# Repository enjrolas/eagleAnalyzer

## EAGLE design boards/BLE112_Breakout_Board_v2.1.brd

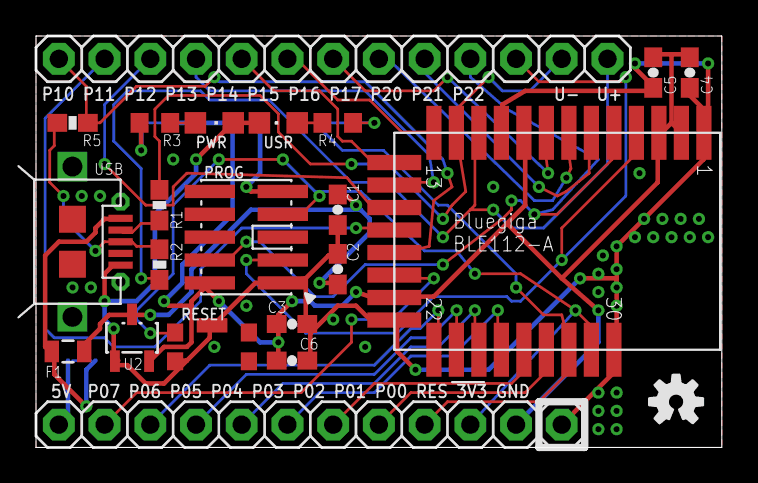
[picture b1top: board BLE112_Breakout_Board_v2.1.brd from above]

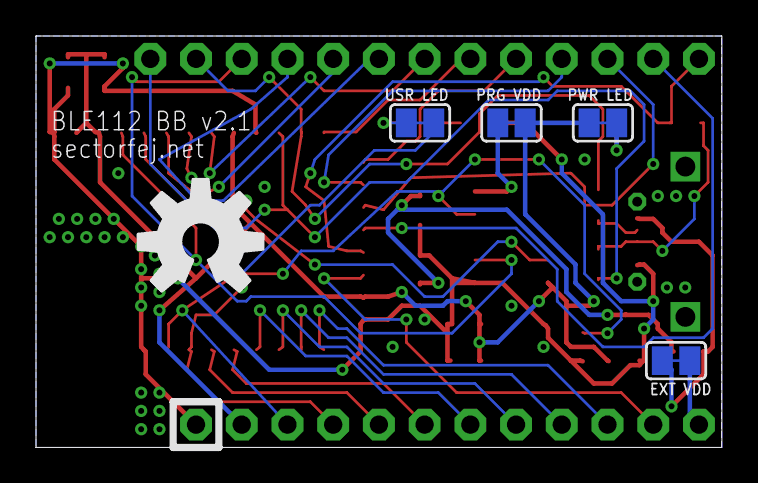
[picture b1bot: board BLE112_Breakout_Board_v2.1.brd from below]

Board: 2 copper layers, 38.1 x 22.9 mm, 27 parts (5 on the bottom side), 34 nets.

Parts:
C1: 0.47uF; 0603-CAP
C2, C3: 2.2uF; 0603-CAP
C4, C5, C6: 1uF; 0603-CAP
F1: 1K; 0805
JP1: BRK1; 1X12
JP2: BRK1; 1X13
OSHW1: OSHW-LOGOL; OSHW-LOGO-L
OSHW2: OSHW-LOGOS; OSHW-LOGO-S
PROG: CONN_5-2-FTSH-V; FTSH-105-DV
PWR: GREEN; CHIPLED_0805
R1, R2: 33; 0603-RES
R3, R4: 470; R0603
R5: 1.5K; 0603-RES
S1: RESET; 101-IG
SJ1: PRG VDD; SJ
SJ2: PWR LED; SJ
SJ3: USR LED; SJ
SJ4: EXT VDD; SJ
U1: BLE112-A
U2: MCP1700; SOT23-3
USB: MICROUSB-47589-0001
USR: BLUE; CHIPLED_0805

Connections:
3.3V: C3.1, C4.1, C5.1, C6.2, JP1.2, PROG.2, SJ1.2, SJ2.1, U1.AVDD1, U1.AVDD2, U1.DVDD, U1.VDD_USB, U2.2
5V: C1.1, C2.1, F1.1, U2.3
EXT5V: JP1.12, SJ4.2
GND: C1.2, C2.2, C3.2, C4.2, C5.2, C6.1, JP1.1, PROG.1, PWR.C, S1.2, S1.GND, U1.GND1, U1.GND2, U1.GND3, U1.GND4, U2.1, USB.GND, USR.C
unnamed: PWR.A, R3.2
unnamed: R3.1, SJ2.2
unnamed: R4.2, USR.A
unnamed: R4.1, SJ3.2
P0_0: JP1.4, SJ3.1, U1.P0_0
P0_1: JP1.5, U1.P0_1
P0_2: JP1.6, U1.P0_2
P0_3: JP1.7, U1.P0_3
P0_4: JP1.8, U1.P0_4
P0_5: JP1.9, U1.P0_5
P0_6: JP1.10, U1.P0_6
P0_7: JP1.11, U1.P0_7
P1_0: JP2.13, R5.2, U1.P1_0
P1_1: JP2.12, U1.P1_1
P1_2: JP2.11, U1.P1_2
P1_3: JP2.10, U1.P1_3
P1_4: JP2.9, U1.P1_4
P1_5: JP2.8, U1.P1_5
P1_6: JP2.7, U1.P1_6
P1_7: JP2.6, U1.P1_7
P2_0: JP2.5, U1.P2_0
P2_1: JP2.4, PROG.4, U1.P2_1
P2_2: JP2.3, PROG.3, U1.P2_2
PRG_VDD: PROG.9, SJ1.1
P_U+: R2.2, R5.1, USB.D+
P_U-: R1.2, USB.D-
RESET: JP1.3, PROG.7, S1.1, U1.RESET
USB+: JP2.1, R2.1, U1.USB+
USB-: JP2.2, R1.1, U1.USB-
VBUS: F1.2, SJ4.1, USB.VBUS

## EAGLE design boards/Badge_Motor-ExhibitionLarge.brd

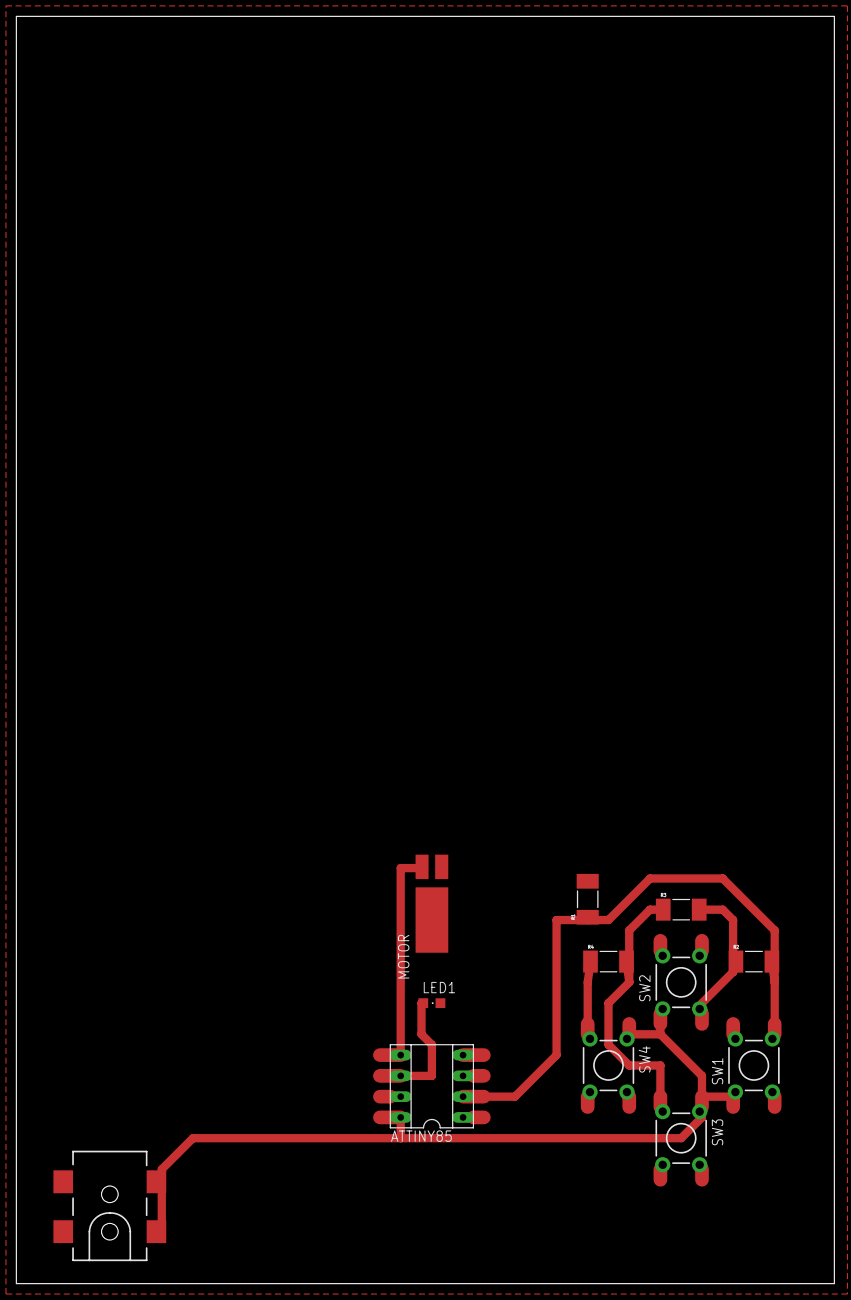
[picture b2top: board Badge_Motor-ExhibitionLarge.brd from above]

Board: 2 copper layers, 100.0 x 154.9 mm, 12 parts (0 on the bottom side), 8 nets.

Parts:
ATTINY85: SOCKET-08
LED1: CHIPLED_0805
MOTOR: VIB-MOTOR
POWER: 3-5VDC; POWER_JACK_SMD
R1, R2, R3, R4: R2010
SW1, SW2, SW3, SW4: TACTILE-PTH

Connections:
+3V: ATTINY85.8, POWER.GND, POWER.P$4, SW1.1, SW2.1, SW3.1, SW4.1
GND: ATTINY85.4, LED1.C, MOTOR.1, POWER.VIN0, R1.2
unnamed: ATTINY85.5, MOTOR.2
unnamed: ATTINY85.2, R1.1, R2.2, SW1.4
unnamed: ATTINY85.6, LED1.A
unnamed: R4.1, SW4.3
unnamed: R3.1, R4.2, SW3.3
unnamed: R2.1, R3.2, SW2.3

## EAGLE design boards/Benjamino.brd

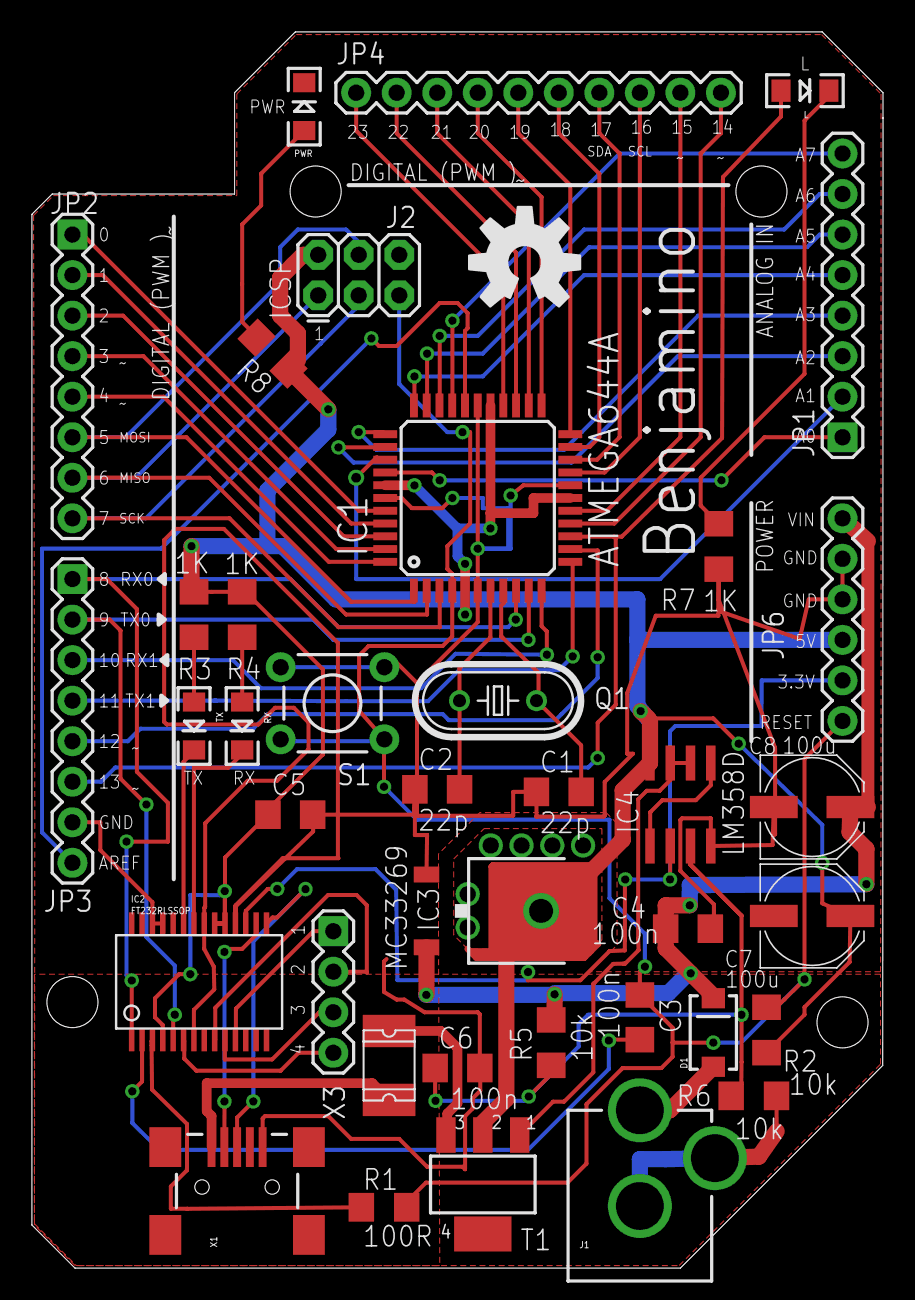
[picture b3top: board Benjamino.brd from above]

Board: 2 copper layers, 53.3 x 77.5 mm, 40 parts (1 on the bottom side), 60 nets.

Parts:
C1, C2: 22p; C1206
C3, C4, C5, C6: 100n; C1206
C7, C8: 100u; PANASONIC_D
D1: SMA-DIODE
F1: 0.5A; 1812L
IC1: ATMEGA644A; TQFP44
IC2: FT232RLSSOP; SSOP28DB
IC3: MC33269; DPACK
IC4: LM358D; SO08
J1: POWER_JACKPTH; POWER_JACK_PTH
J2: ICSP; 2X3
JP1, JP2, JP3: 1X08
JP4: 1X10
JP6: 1X06
L: LED-1206
PWR: LED-1206
Q1: HC49U-V
R1: 100R; R1206
R2, R5, R6: 10k; R1206
R3, R4, R7, R8: 1K; R1206
RX: LED-1206
S1: TACTILE-PTH
T1: SOT223
TX: LED-1206
U$1, U$2: OSHW-LOGO-L
X1: USBSMD; USB-MINIB
X3: 1X04

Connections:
3V3: IC2.17, IC4.2, JP6.2
AREF: IC1.29, JP3.8
GND: C1.1, C2.1, C4.2, C5.2, C6.2, C7.-, C8.-, IC1.6, IC1.18, IC1.28, IC1.39, IC2.7, IC2.18, IC2.21, IC2.25, IC2.26, IC3.1, IC4.4, J1.GND, J1.GNDBREAK, J2.6, JP3.7, JP6.4, JP6.5, PWR.C, R6.1, R7.1, S1.3, S1.4, X1.GND
MISO: IC1.2, J2.1, JP2.7
MOSI: IC1.1, J2.4, JP2.6
unnamed: IC1.37, JP1.1
unnamed: IC1.36, JP1.2
unnamed: IC1.35, JP1.3
unnamed: IC1.34, JP1.4
unnamed: IC1.33, JP1.5
unnamed: IC1.32, JP1.6
unnamed: C1.2, IC1.8, Q1.1
unnamed: C2.2, IC1.7, Q1.2
unnamed: IC1.31, JP1.7
unnamed: IC1.30, JP1.8
unnamed: IC2.15, X1.D+
unnamed: IC2.16, X1.D-
unnamed: IC1.26, JP4.1
unnamed: IC1.25, JP4.2
unnamed: IC1.24, JP4.3
unnamed: IC1.23, JP4.4
unnamed: D1.A, J1.PWR
unnamed: IC1.11, JP3.3
unnamed: IC1.12, JP3.4
unnamed: IC1.13, JP3.5
unnamed: IC1.14, JP3.6, L.A
unnamed: IC1.22, JP4.5
unnamed: IC1.21, JP4.6
unnamed: IC1.20, JP4.7
unnamed: IC1.19, JP4.8
unnamed: IC1.16, JP4.9
unnamed: IC1.15, JP4.10
unnamed: IC1.40, JP2.1
unnamed: IC1.41, JP2.2
unnamed: IC1.42, JP2.3
unnamed: IC1.43, JP2.4
unnamed: IC2.11, X3.1
unnamed: IC2.9, X3.2
unnamed: IC2.10, X3.3
unnamed: IC2.6, X3.4
unnamed: IC2.3, R1.1
unnamed: C3.2, IC2.2
unnamed: IC2.22, RX.C
unnamed: IC2.23, TX.C
unnamed: R3.1, TX.A
unnamed: R4.1, RX.A
unnamed: F1.P$1, X1.VBUS
unnamed: C6.1, IC4.3, R5.1, R6.2
unnamed: IC4.1, IC4.5
unnamed: IC4.6, IC4.7, T1.1
unnamed: L.C, R7.2
unnamed: PWR.A, R8.2
RESET: C3.1, IC1.4, J2.5, JP6.1, R1.2, R2.2, S1.1, S1.2
RXD: IC1.9, IC2.1, JP3.1
SCK: IC1.3, J2.3, JP2.8
SS: IC1.44, JP2.5
TXD: IC1.10, IC2.5, JP3.2
USBVCC: F1.P$2, T1.3
VCC: C5.1, C7.+, IC1.5, IC1.17, IC1.27, IC1.38, IC2.4, IC2.19, IC2.20, IC3.2, IC4.8, J2.2, JP6.3, R2.1, R3.2, R4.2, R8.1, T1.2
VIN: C4.1, C8.+, D1.C, IC3.3, JP6.6, R5.2

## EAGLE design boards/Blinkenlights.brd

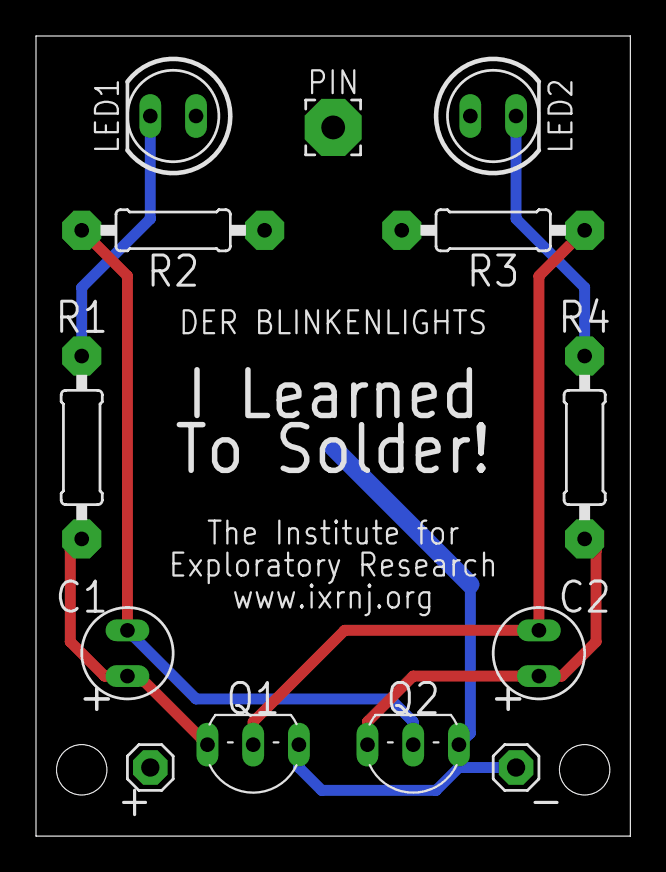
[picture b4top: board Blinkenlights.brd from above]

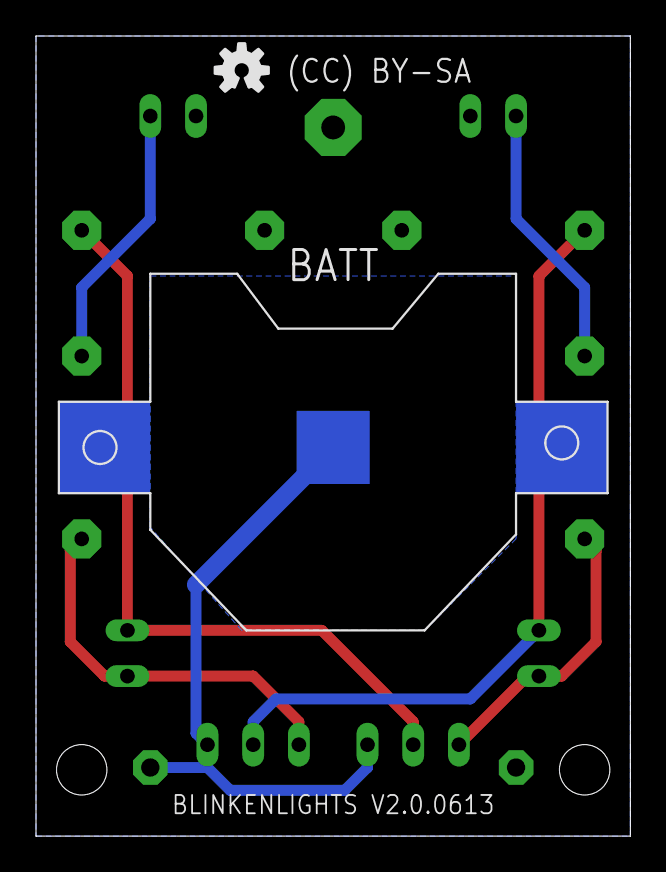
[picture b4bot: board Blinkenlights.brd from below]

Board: 4 copper layers, 33.0 x 44.5 mm, 15 parts (2 on the bottom side), 8 nets.

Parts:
+: 1X01
-: 1X01
BATT: CR2032; CR2032-SMD
C1, C2: 10μF; E-2.54-05
LED1, LED2: LED5MM_BIG
PIN: 3,17/1,3
Q1, Q2: 2N2222; TO92-EBC-OVAL
R1, R4: 220Ω; 0207/10_BIG
R2, R3: 100kΩ; 0207/10_BIG
U$1: OSHW-LOGO-S

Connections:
GND: -.1, BATT.-, Q1.E, Q2.E
unnamed: C1.+, Q1.C, R1.1
unnamed: C2.+, Q2.C, R4.1
unnamed: C1.-, Q2.B, R2.1
unnamed: C2.-, Q1.B, R3.1
unnamed: LED1.K, R1.2
unnamed: LED2.K, R4.2
VCC: +.1, BATT.+$1, BATT.+$2, LED1.A, LED2.A, R2.2, R3.2

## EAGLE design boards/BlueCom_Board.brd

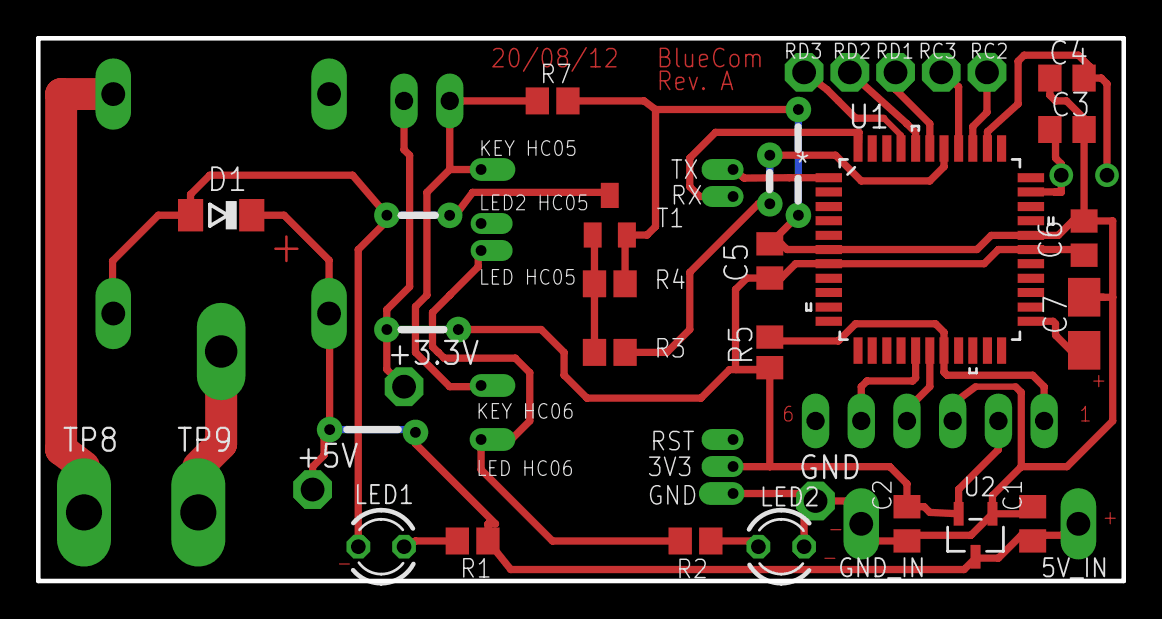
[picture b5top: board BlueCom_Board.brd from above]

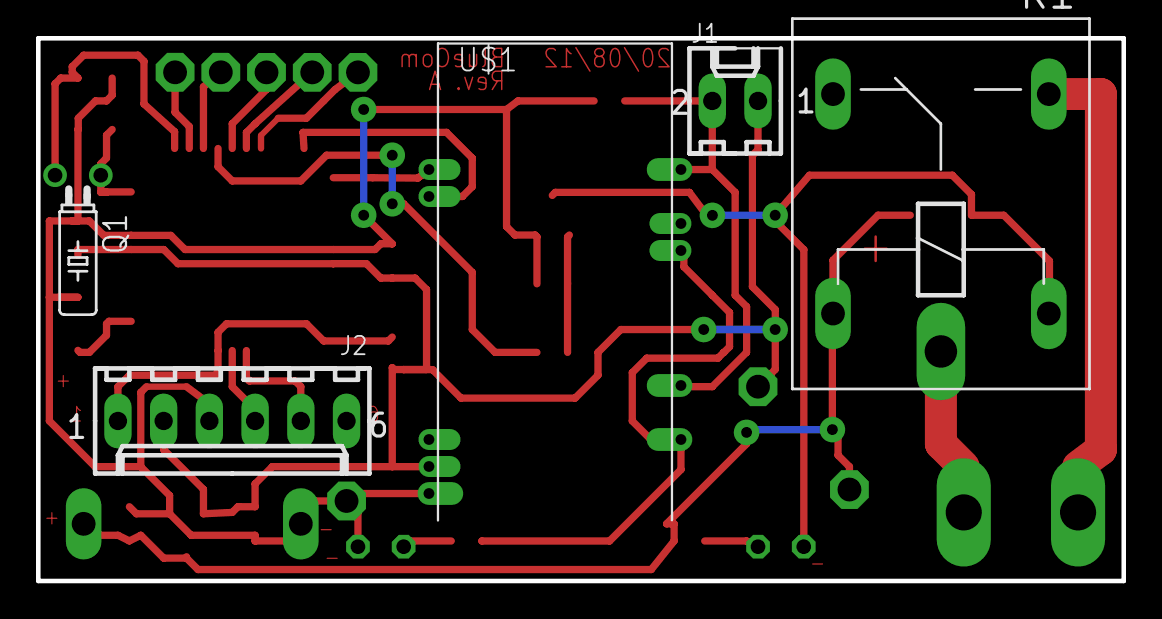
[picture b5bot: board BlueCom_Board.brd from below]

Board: 2 copper layers, 60.3 x 30.1 mm, 36 parts (5 on the bottom side), 25 nets.

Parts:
5V_IN: TPPAD1-13Y; P1-13Y
+3.3V, +5V: TPPAD1-13; P1-13
C1, C2: 1µF 25V; C0805
C3, C4: 12pF; C0805
C5, C6: 100nF; C0805
C7: 10 µF; A/3216-18W
D1: LL4148; SOD80C
GND: TPPAD1-13; P1-13
GND_IN: TPPAD1-13Y; P1-13Y
J1: Con 2.45mm; 6410-02
J2: Con 5pts 2.54mm; 6410-06
K1: Relay 5V; ZF112
LED1: Green 3mm; LED3MM
LED2: Blue 3mm; LED3MM
Q1: 32.768 kHz; TC26H
R1, R2: 680; R0805
R3: 5.6K; R0805
R4: 47K; R0805
R5, R7: 10K; R0805
RC2, RC3: TPPAD1-13; P1-13
RD1, RD2, RD3: TPPAD1-13; P1-13
T1: BC846; SOT23
TP8, TP9: TPPAD1-13Y; P1-20Y
U1: PIC18F44J11-I/PT; QFP80P1200X1200X120-44N
U2: MCP1702T-3302E/CB; SOT95P255X145-3N
U$1: BLUETOOTH_TRAVERSANT

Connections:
+3V3: +3.3V.TP, C2.1, C5.1, C6.1, J1.1, J2.2, R5.1, U1.7, U1.28, U2.2, U$1.12
+5V: 5V_IN.TP, +5V.TP, C1.1, D1.C, K1.1, R1.2, U2.3
GND: C1.2, C2.2, C3.2, C4.2, C5.2, C6.2, C7.-, GND.TP, GND_IN.TP, J2.3, LED2.K, R4.1, R7.1, T1.2, U1.6, U1.29, U2.1, U$1.13
unnamed: D1.A, K1.2, LED1.K, T1.3
unnamed: R3.1, R4.2, T1.1
unnamed: RD3.TP, U1.41
unnamed: LED1.A, R1.1
unnamed: LED2.A, R2.1
unnamed: R2.2, U$1.24, U$1.31
unnamed: J1.2, R7.2, U$1.26, U$1.34
unnamed: U1.44, U$1.2
unnamed: U1.1, U$1.1
unnamed: K1.S, TP8.TP
unnamed: K1.P, TP9.TP
unnamed: J2.1, R5.2, U1.18
unnamed: C4.1, Q1.2, U1.35
unnamed: C3.1, Q1.1, U1.32
unnamed: J2.5, U1.16
unnamed: RD2.TP, U1.40
unnamed: C7.+, U1.23
unnamed: R3.2, U1.38
unnamed: J2.4, U1.17
unnamed: RD1.TP, U1.39
unnamed: RC2.TP, U1.36
unnamed: RC3.TP, U1.37

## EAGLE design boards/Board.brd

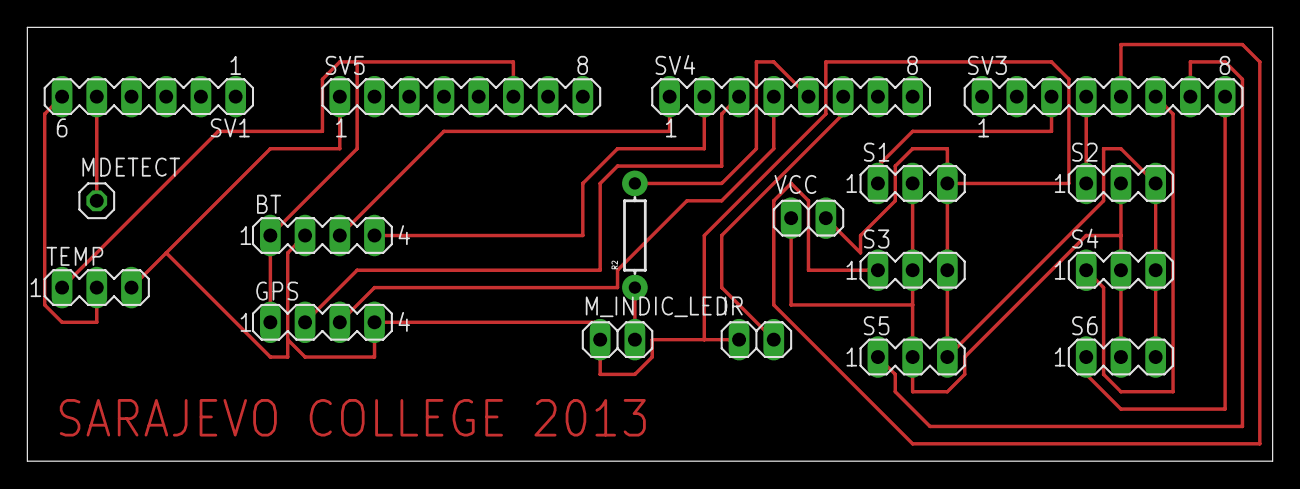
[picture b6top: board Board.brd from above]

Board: 2 copper layers, 91.1 x 31.7 mm, 18 parts (0 on the bottom side), 18 nets.

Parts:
BT: MA04-1
GPS: MA04-1
IR: 1X02
MDETECT: 1X01
M_INDIC_LED: 1X02
R2: AXIAL-0.3
S1, S2, S3, S4, S5, S6: MA03-1
SV1: MA06-1
SV3, SV4, SV5: MA08-1
TEMP: MA03-1
VCC: 1X02

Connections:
unnamed: S1.1, SV3.3
unnamed: BT.1, GPS.1, SV5.6, TEMP.1
unnamed: S2.1, SV3.4
unnamed: S3.1, SV3.5
unnamed: S4.1, SV3.6
unnamed: S5.1, SV3.7
unnamed: S6.1, SV3.8
unnamed: BT.2, GPS.4, IR.1, M_INDIC_LED.1, S1.3, S2.3, S3.3, S4.3, S5.3, S6.3, SV5.1, TEMP.3, VCC.2
unnamed: SV1.6, TEMP.2
unnamed: BT.4, SV4.2
unnamed: MDETECT.1, SV1.5
unnamed: M_INDIC_LED.2, R2.P$1
unnamed: S1.2, S2.2, S3.2, S4.2, S5.2, S6.2, VCC.1
unnamed: R2.P$2, SV4.5
unnamed: IR.2, SV4.6
unnamed: BT.3, SV4.1
unnamed: GPS.2, SV4.3
unnamed: GPS.3, SV4.4

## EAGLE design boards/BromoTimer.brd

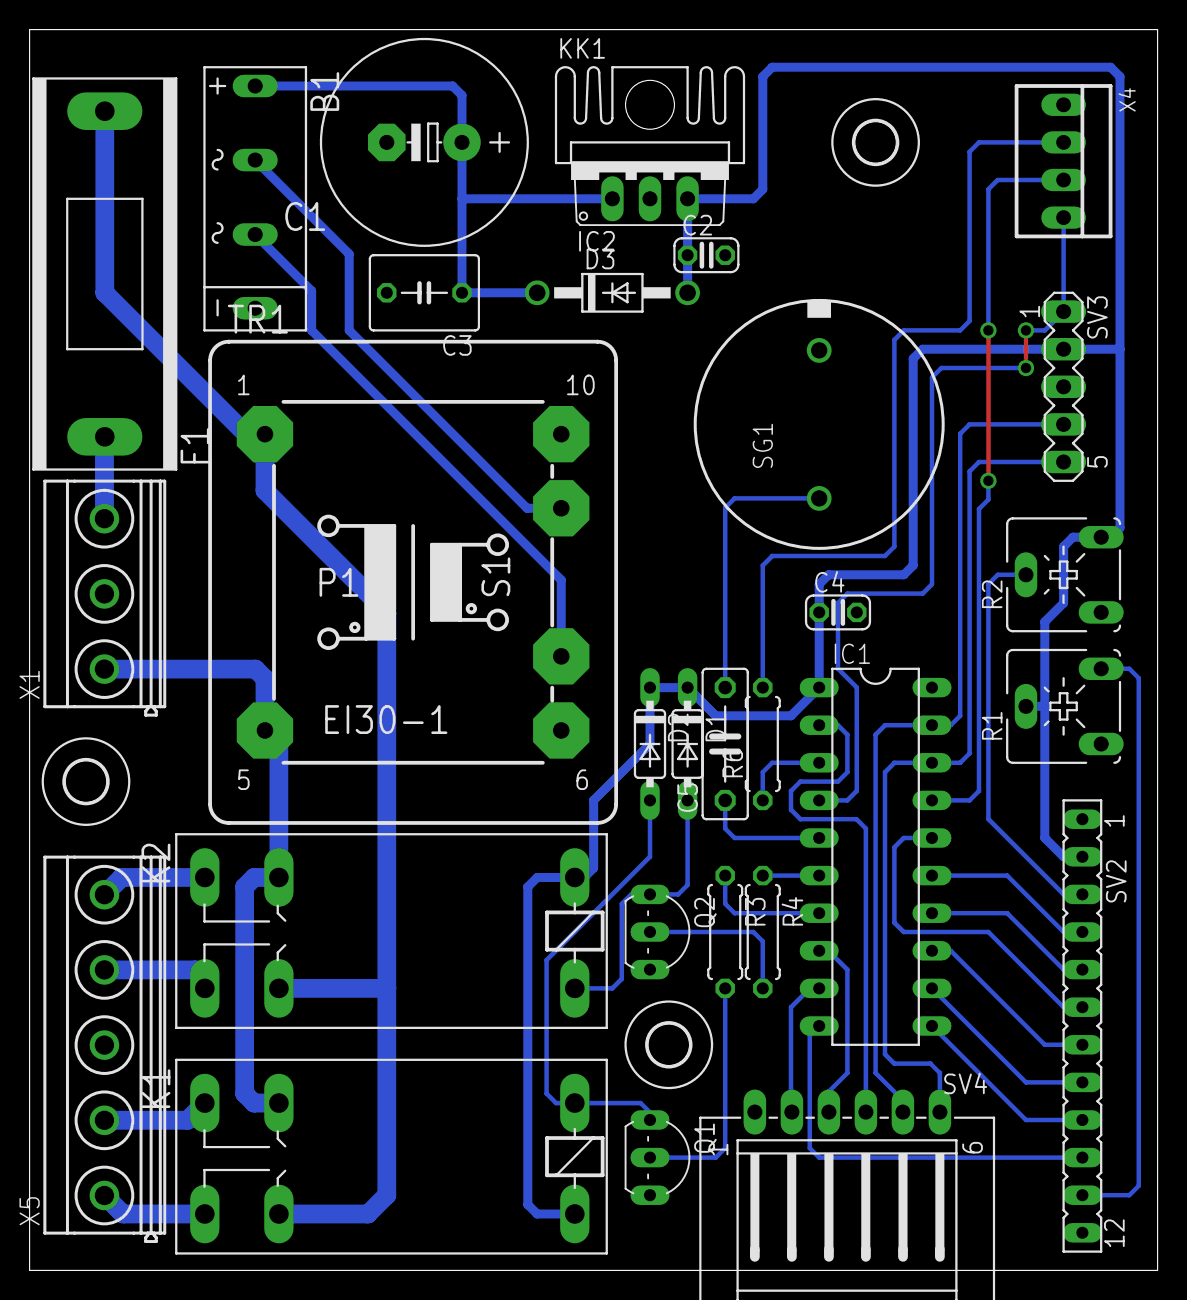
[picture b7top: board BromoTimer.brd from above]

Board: 2 copper layers, 76.2 x 83.8 mm, 33 parts (0 on the bottom side), 38 nets.

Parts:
B1: 500mA; 2KBB-R
C1: 1m; E5-13
C2: 100n; C025-024X044
C3: 330n; C050-050X075
C4: 10n; C025-024X044
C5: 100n; C075-032X103
D1, D2: 1N4148DO35-7; DO35-7
D3: 1N4004; DO41-10
F1: 250V-500mA; SH22
IC1: PIC16F687; DIP20
IC2: 7805TV; TO220V
K1, K2: G2R2A
KK1: SK95-2M3
Q1, Q2: BC548B; TO92-EBC
R1, R2: 10k; CA6V
R3, R4: 1k; 0207/7
R6: 470; 0207/7
SG1: EFBAA40D101
SV2: DISPLAY; FE12
SV3: ICSP; MA05-1
SV4: ENCODER; L06P
TR1: 220/12; EI30-1
U$2, U$3, U$4: 2,8
X1: AC_IN; MKDSN1,5/3-5,08
X4: 22-23-2041
X5: AC_OUT; MKDSN1,5/5-5,08

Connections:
+5V: C2.1, C4.1, D1.C, D2.C, D3.A, IC1.1, IC2.3, K1.2, K2.1, R1.S, R2.E, SV2.2, SV3.2
A: IC1.19, SV3.4, SV4.5
AC1: K1.P2, K2.P2, TR1.5, X1.1
AC2: F1.2, K1.P1, K2.P1, TR1.1
B: IC1.18, SV3.5, SV4.6
B0: IC1.13, SV2.7
B1: IC1.12, SV2.8
B2: IC1.11, SV2.9
B3: IC1.10, SV2.10
EN: IC1.16, SV2.6
GND: B1.-, C1.-, C2.2, C3.2, C4.2, IC1.20, IC2.2, Q1.E, Q2.E, R2.A, SG1.2, SV2.1, SV2.12, SV3.3, SV4.1, X4.1
LG: IC1.9, SV4.2
LR: IC1.8, SV4.3
unnamed: R1.E, SV2.11
unnamed: B1.AC2, TR1.7
unnamed: R2.S, SV2.3
unnamed: Q2.B, R4.2
unnamed: Q1.B, R3.2
unnamed: D1.A, K2.2, Q2.C
unnamed: D2.A, K1.1, Q1.C
unnamed: K1.S1, X5.1
unnamed: K1.S2, X5.2
unnamed: K2.S1, X5.4
unnamed: K2.S2, X5.5
unnamed: B1.AC1, TR1.9
unnamed: IC1.17, X4.3
unnamed: IC1.6, R4.1
unnamed: IC1.4, SV3.1, X4.4
unnamed: IC1.7, R3.1
unnamed: C5.1, IC1.5
unnamed: C5.2, SG1.1
unnamed: IC1.3, R6.1
unnamed: R6.2, X4.2
unnamed: F1.1, X1.3
RS: IC1.15, SV2.4
RW: IC1.14, SV2.5
SW: IC1.2, SV4.4
V+: B1.+, C1.+, C3.1, D3.C, IC2.1

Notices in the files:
boards/Benjamino.brd:
licensed under the
Modified BSD License.
parts and their libraries:
SparkFun: Licensing: CC v3.0 Share-Alike You are welcome to use this library for commercial purposes.
